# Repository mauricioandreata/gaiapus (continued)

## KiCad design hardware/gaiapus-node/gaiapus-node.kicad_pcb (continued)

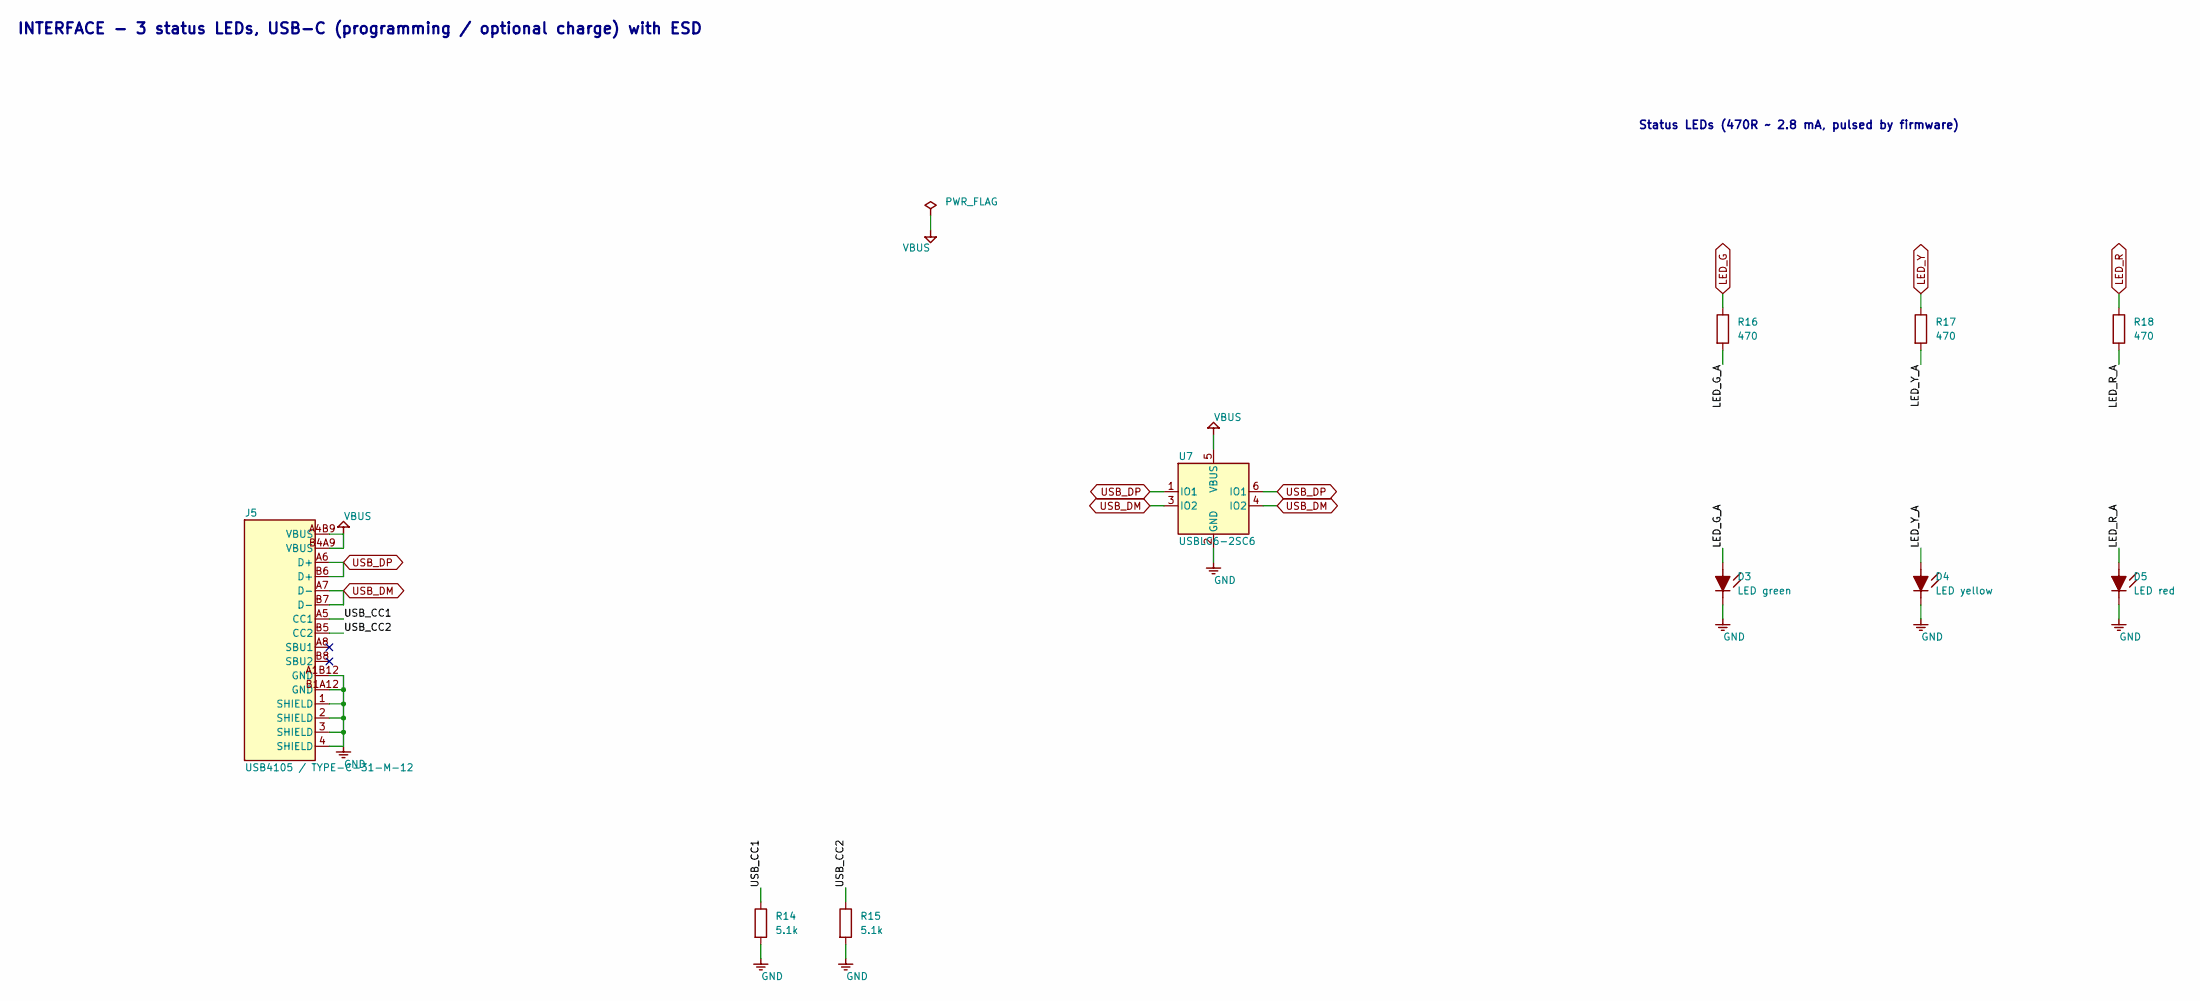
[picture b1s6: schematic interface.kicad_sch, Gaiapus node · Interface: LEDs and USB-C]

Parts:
D3: LED green; LED_0603_1608Metric; LCSC TBD
D4: LED yellow; LED_0603_1608Metric; LCSC TBD
D5: LED red; LED_0603_1608Metric; LCSC TBD
J5: USB4105 / TYPE-C-31-M-12; USB-C_SMD-TYPE-C-31-M-12_1; MPN TYPE-C-31-M-12; LCSC C165948
R14, R15: 5.1k; R_0603_1608Metric; LCSC TBD
R16, R17, R18: 470; R_0603_1608Metric; LCSC TBD
U7: USBLC6-2SC6; SOT-23-6_L2.9-W1.6-P0.95-LS2.8-BL; MPN USBLC6-2SC6; LCSC C7519

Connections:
/Interface/LED_G_A: D3.2 (A), R16.2
/Interface/LED_R_A: D5.2 (A), R18.2
/Interface/LED_Y_A: D4.2 (A), R17.2
/Interface/USB_CC1: J5.A5 (CC1), R14.1
/Interface/USB_CC2: J5.B5 (CC2), R15.1
LED_G: R16.1; also elsewhere on the board
LED_R: R18.1; also elsewhere on the board
LED_Y: R17.1; also elsewhere on the board
USB_DM: J5.A7 (D-), J5.B7 (D-), U7.3 (IO2), U7.4 (IO2); also elsewhere on the board
USB_DP: J5.A6 (D+), J5.B6 (D+), U7.1 (IO1), U7.6 (IO1); also elsewhere on the board
VBUS: J5.A4B9 (VBUS), J5.B4A9 (VBUS), U7.5 (VBUS); also elsewhere on the board

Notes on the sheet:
INTERFACE - 3 status LEDs, USB-C (programming / optional charge) with ESD
Status LEDs (470R ~ 2.8 mA, pulsed by firmware)

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
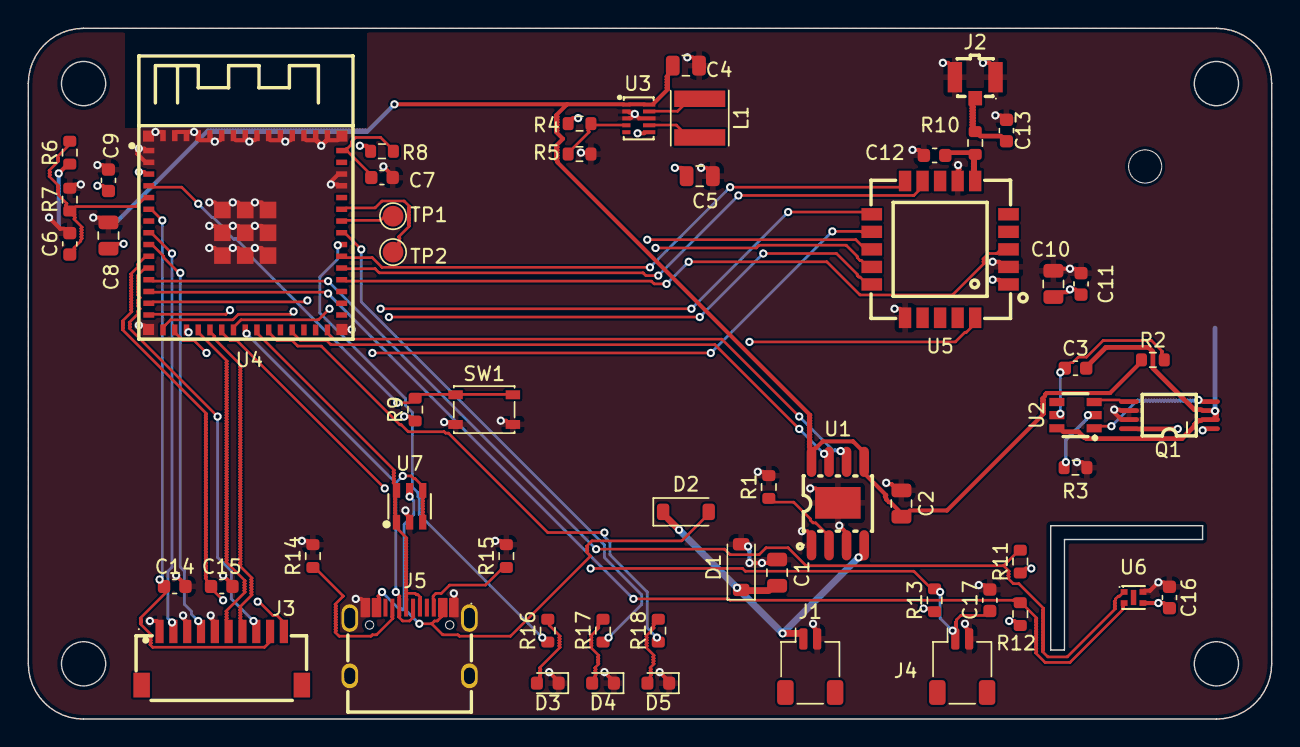
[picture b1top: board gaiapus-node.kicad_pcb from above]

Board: 4 copper layers, 90.0 x 50.0 mm, 58 parts (1 on the bottom side), 53 nets.

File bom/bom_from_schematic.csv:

Board,Refs,Qty,Value,Footprint,Manufacturer,MPN,LCSC,DNP
head,J1,1,SOLAR 5V 60mA,Connector_JST:JST_SH_SM02B-SRSS-TB_1x02-1MP_P1.00mm_Horizontal,JST,SM02B-SRSS-TB,TBD,
head,D1,1,BZT52C6V2,Diode_SMD:D_SOD-123,,BZT52C6V2,TBD,
head,C1 C2 C4 C8 C10,5,10uF,Capacitor_SMD:C_0805_2012Metric,,,TBD,
head,D2,1,B5819W,Diode_SMD:D_SOD-123,,,TBD,
head,U1,1,CN3058E,lcsc:SOIC-8_L4.9-W3.9-P1.27-LS6.0-BL-EP3.3,Consonance,CN3058E,C112011,
head,R1,1,24k 1%,Resistor_SMD:R_0603_1608Metric,,,TBD,
head,BT1,1,18650 LiFePO4,lcsc:BATTERY-SMD_18650-1S-L77.1-W20.7-1,MYOUNG,BH-18650-B1BA002,C2988620,
head,R2,1,100,Resistor_SMD:R_0603_1608Metric,,,TBD,
head,C3 C6 C9 C11 C16,5,100nF,Capacitor_SMD:C_0603_1608Metric,,,TBD,
head,U2,1,HY2112-BB,lcsc:SOT-23-6_L2.9-W1.6-P0.95-LS2.8-BR,HYCON,HY2112-BB,C161942,
head,Q1,1,8205A,lcsc:TSSOP-8_L4.4-W3.0-P0.65-LS6.4-BL,HXY MOSFET,8205A,C5148694,
head,R3,1,2k,Resistor_SMD:R_0603_1608Metric,,,TBD,
head,U3,1,TPS63802,lcsc:VSON-10_L3.0-W2.0-P0.50-TL,Texas Instruments,TPS63802DLAR,C2845237,
head,L1,1,0.47uH,Inductor_SMD:L_Taiyo-Yuden_NR-40xx,,,TBD,
head,C5,1,22uF,Capacitor_SMD:C_0805_2012Metric,,,TBD,
head,R4,1,511k,Resistor_SMD:R_0603_1608Metric,,,TBD,
head,R5,1,91k,Resistor_SMD:R_0603_1608Metric,,,TBD,
head,R6 R7,2,2.2M,Resistor_SMD:R_0603_1608Metric,,,TBD,
head,U4,1,ESP32-S3-MINI-1-N8,lcsc:BULETM-SMD_ESP32-S3-MINI-1-N8,Espressif,ESP32-S3-MINI-1-N8,C2913206,
head,R8 R9 R11 R12,4,10k,Resistor_SMD:R_0603_1608Metric,,,TBD,
head,C7,1,1uF,Capacitor_SMD:C_0603_1608Metric,,,TBD,
head,SW1,1,USER/BOOT,Button_Switch_SMD:SW_SPST_PTS810,,,TBD,
head,TP1,1,TP_TX,TestPoint:TestPoint_Pad_D1.5mm,,,TBD,
head,TP2,1,TP_RX,TestPoint:TestPoint_Pad_D1.5mm,,,TBD,
head,U5,1,E22-900MM22S,lcsc:WIRELM-SMD_20P-L10.0-W10.0-P1.27-TL,EBYTE,E22-900MM22S,C5333985,
head,R10,1,0R,Resistor_SMD:R_0603_1608Metric,,,TBD,
head,C12 C13,2,DNP,Capacitor_SMD:C_0603_1608Metric,,,TBD,DNP
head,J2,1,U.FL-R-SMT-1(80),lcsc:RF-SMD_FRF05002-JSS103M,Hirose,U.FL-R-SMT-1(80),C88374,
head,J3,1,PROBE,lcsc:CONN-SMD_10P-P1.00_SM10B-SRSS-TB-LF-SN,JST,SM10B-SRSS-TB(LF)(SN),C160409,
head,C14 C15 C17,3,10nF,Capacitor_SMD:C_0603_1608Metric,,,TBD,
head,U6,1,SHT40-AD1B-R2,lcsc:DFN-4_L1.5-W1.5-P0.8-TL-EP,Sensirion,SHT40-AD1B-R2,C2909890,
head,J4,1,RAIN,Connector_JST:JST_SH_SM02B-SRSS-TB_1x02-1MP_P1.00mm_Horizontal,JST,SM02B-SRSS-TB,TBD,
head,R13,1,470k,Resistor_SMD:R_0603_1608Metric,,,TBD,
head,J5,1,USB4105 / TYPE-C-31-M-12,lcsc:USB-C_SMD-TYPE-C-31-M-12_1,HRO,TYPE-C-31-M-12,C165948,
head,R14 R15,2,5.1k,Resistor_SMD:R_0603_1608Metric,,,TBD,
head,U7,1,USBLC6-2SC6,lcsc:SOT-23-6_L2.9-W1.6-P0.95-LS2.8-BL,STMicroelectronics,USBLC6-2SC6,C7519,
head,R16 R17 R18,3,470,Resistor_SMD:R_0603_1608Metric,,,TBD,
head,D3,1,LED green,LED_SMD:LED_0603_1608Metric,,,TBD,
head,D4,1,LED yellow,LED_SMD:LED_0603_1608Metric,,,TBD,
head,D5,1,LED red,LED_SMD:LED_0603_1608Metric,,,TBD,
probe,J1,1,HEAD,lcsc:CONN-SMD_10P-P1.00_SM10B-SRSS-TB-LF-SN,JST,SM10B-SRSS-TB(LF)(SN),C160409,
probe,U1 U2,2,74LVC1G14,lcsc:SOT-753_L3.1-W1.7-P0.95-LS3.0-BR,Nexperia,"74LVC1G14GV,125",C131093,
probe,C1 C3,2,100nF,Capacitor_SMD:C_0603_1608Metric,,,TBD,
probe,R1 R3,2,47k,Resistor_SMD:R_0603_1608Metric,,,TBD,
probe,R2 R4,2,100,Resistor_SMD:R_0603_1608Metric,,,TBD,
probe,TP1,1,TP_F15,TestPoint:TestPoint_Pad_D1.5mm,,,TBD,
probe,C2 C4,2,DNP 10pF,Capacitor_SMD:C_0603_1608Metric,,,TBD,DNP
probe,TP2,1,TP_F40,TestPoint:TestPoint_Pad_D1.5mm,,,TBD,
probe,R5 R6,2,10k,Resistor_SMD:R_0603_1608Metric,,,TBD,
probe,RT1,1,NTC 10k 15cm,lcsc:R0603,Murata,NCP18XH103F03RB,C13564,
probe,RT2,1,NTC 10k 40cm,lcsc:R0603,Murata,NCP18XH103F03RB,C13564,

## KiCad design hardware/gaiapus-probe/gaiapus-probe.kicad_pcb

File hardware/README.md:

# Hardware

| Folder | What |
|---|---|
| `gaiapus-node/` | KiCad 8 project of the **head board** (ESP32-S3, LoRa, power, SHT40, rain, LEDs, USB). Root sheet = block diagram. |
| `gaiapus-probe/` | KiCad 8 project of the **probe board** (strip 22 x ~460 mm inside the 32 mm PVC tube): electrodes, oscillators, NTCs. |
| `lib/` | `symbols/gaiapus.kicad_sym` (generated), `footprints/gaiapus.pretty` (electrode), `lcsc.*` (imported from LCSC) |
| `tools/` | generators and checks (below) |

## Tools
| Script | Run when |
|---|---|
| `gen_kicad.py` | after any circuit change: writes both schematics, symbol lib, netlists, `bom/bom_from_schematic.csv` |
| `check_kicad.py` | after `gen_kicad.py`: re-derives connectivity from geometry, must print `RESULT: OK` |
| `gen_footprints.py` | electrode footprint (parametric: width, height, finger, gap) |
| `import_lcsc.cmd` | **on Windows, once**: footprints + 3D models of all LCSC parts (needs Python + internet) |
| `apply_lcsc.py` | after the import: maps footprints, fixes 3D paths, checks pin/pad numbers and pin names against the LCSC symbols |
| `autoplace.py` + `check_placement.py` | first-pass placement into the zones, overlap/edge/hole check |
| `place_head.py` | connectivity-driven floorplan of the head board (positions + rotations), strips routing |
| `fpmove.py` | move/rotate footprints in a board file (90-degree steps) |
| `route.py probe\|head` | grid router (2 layers, 45 deg, vias, GND stitching), clearances from the .kicad_dru; `ROUTE_ONLY`, `ROUTE_FIRST`, `ROUTE_BUDGET`, `ROUTE_RIPUP` (seconds of rip-up and reroute), `ROUTE_MAXHITS` env vars |
| `verify_pcb.py board.kicad_pcb` | independent copper check: connectivity, clearance between nets, copper-to-edge |
| `gen_pcb_outline.py` | board outlines, mounting holes, SHT40 slot and placement boxes (refuses to touch a PCB that already has footprints) |

Close KiCad before regenerating (regeneration overwrites the schematic files).

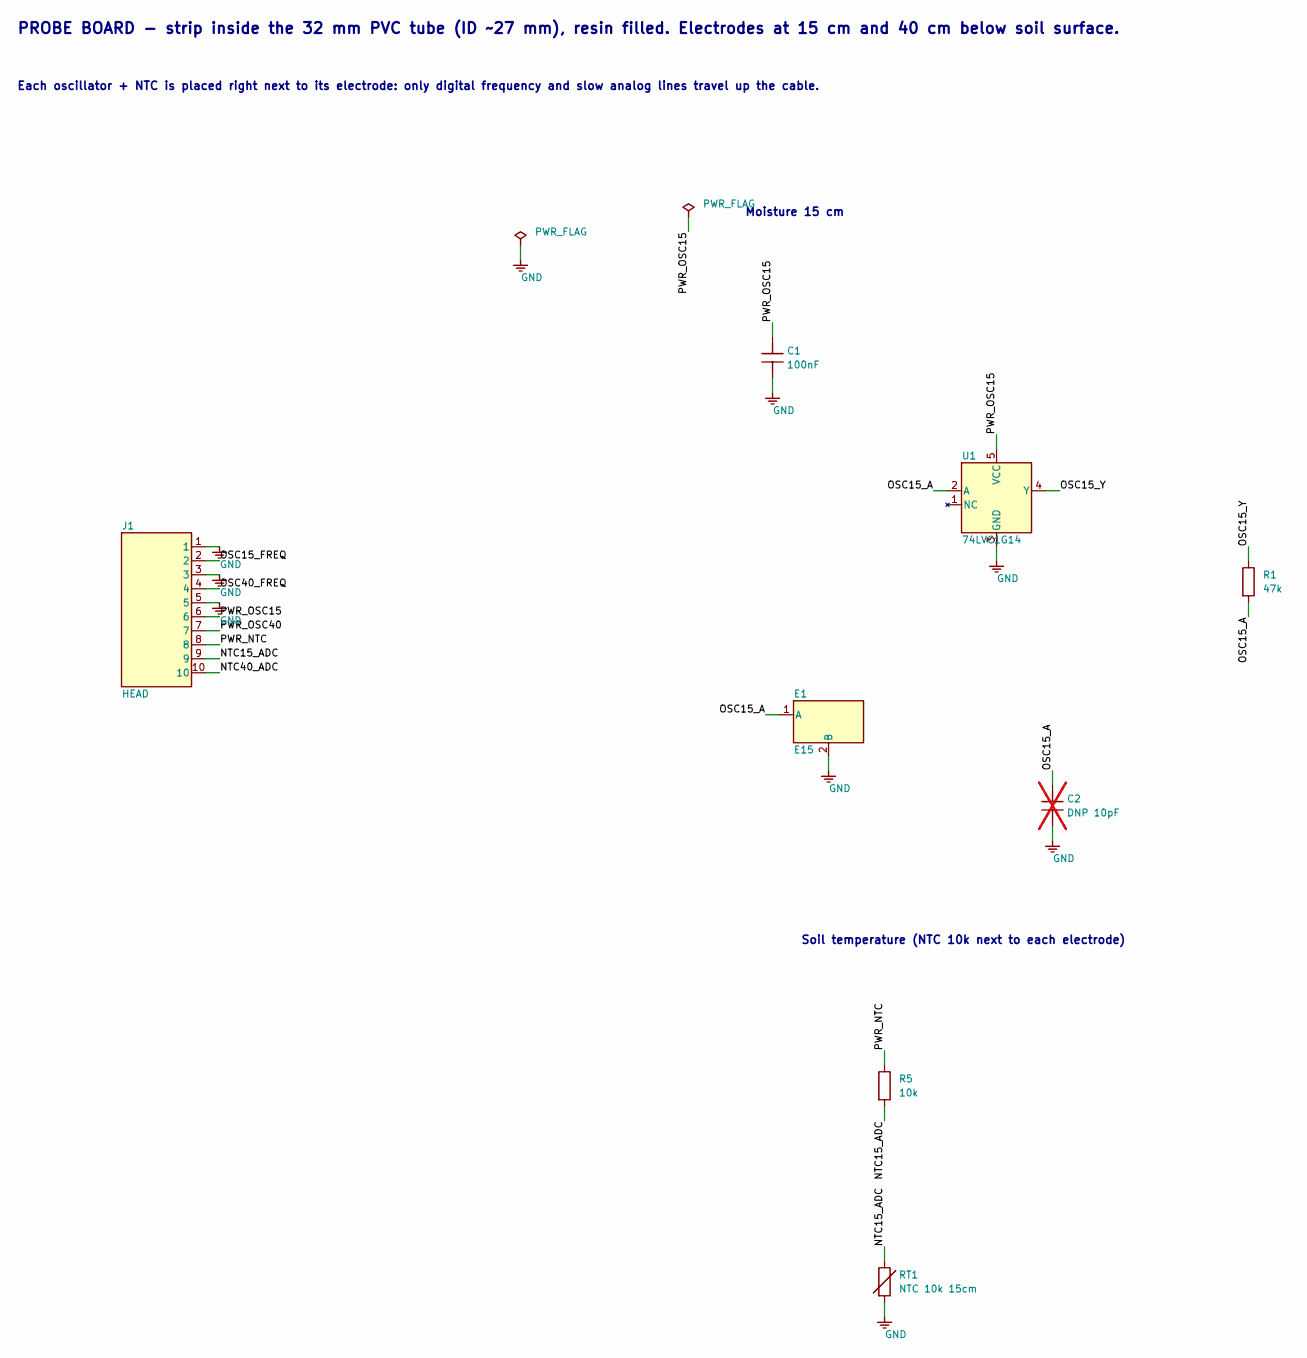
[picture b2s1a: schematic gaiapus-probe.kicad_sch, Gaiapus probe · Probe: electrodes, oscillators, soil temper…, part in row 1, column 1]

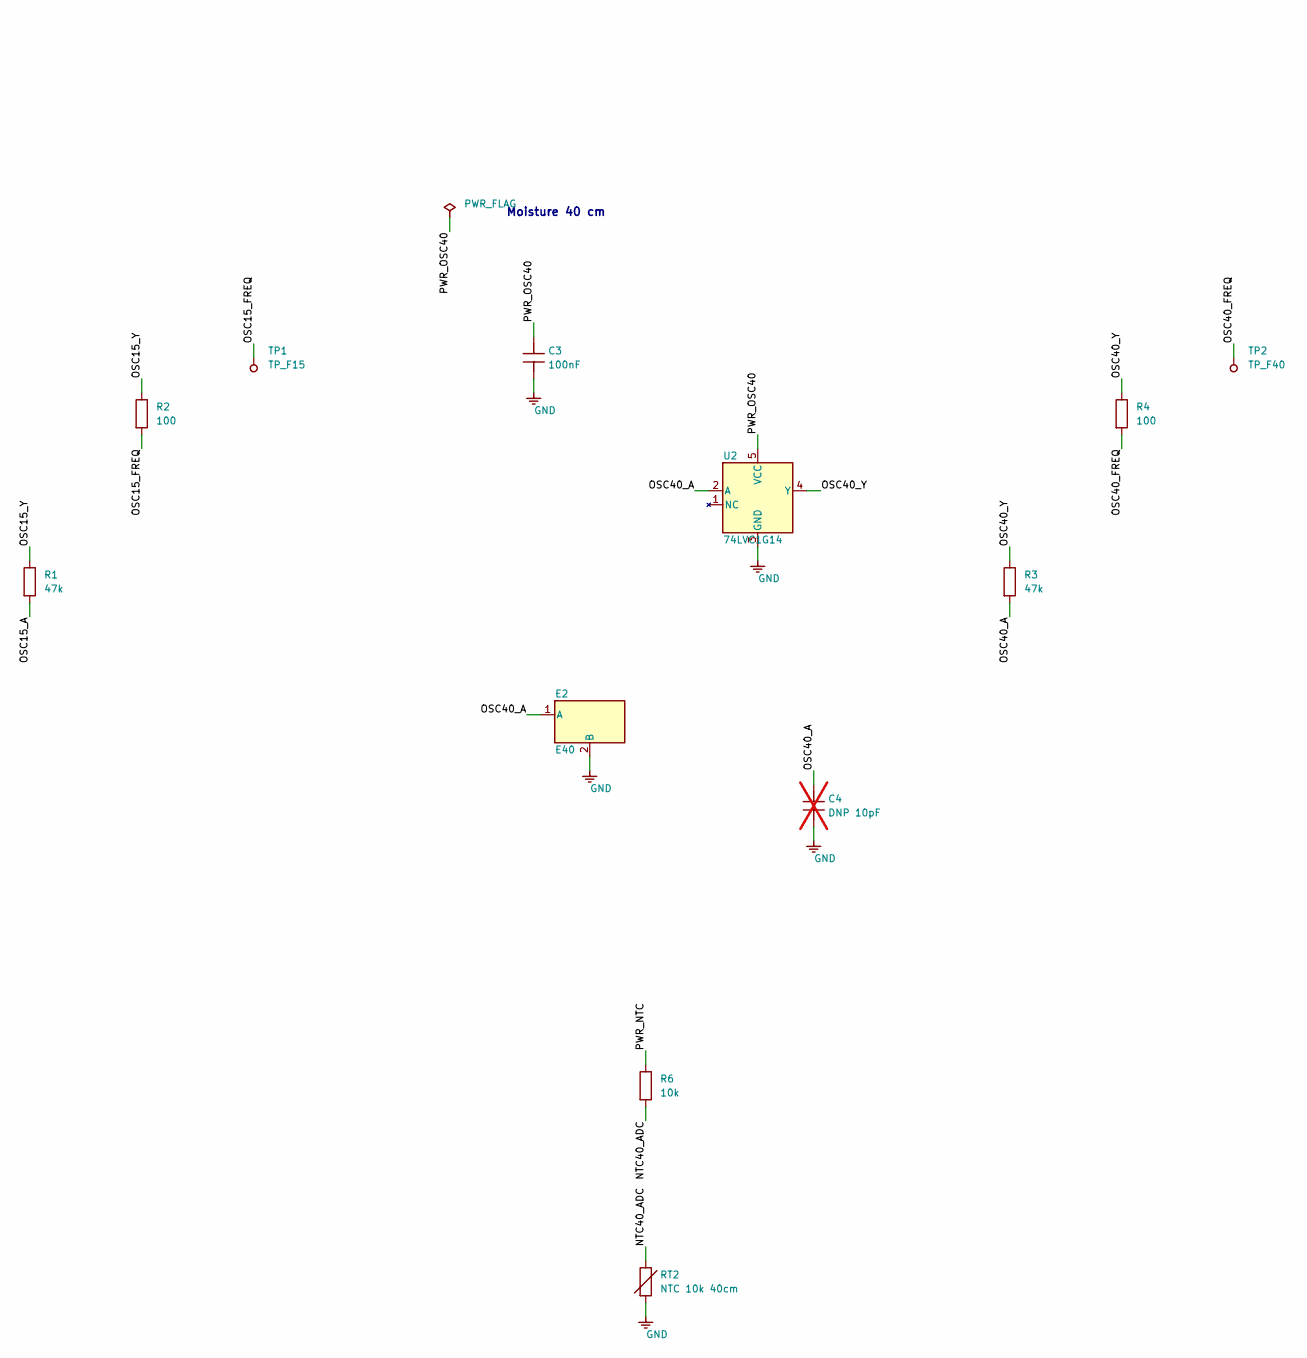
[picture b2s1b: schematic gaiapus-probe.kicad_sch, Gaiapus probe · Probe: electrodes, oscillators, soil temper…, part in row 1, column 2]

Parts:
C1, C3: 100nF; C_0603_1608Metric; LCSC TBD
C2, C4: DNP 10pF; C_0603_1608Metric; LCSC TBD; not fitted
E1: E15; ELECTRODE_IDC_18x40; LCSC TBD
E2: E40; ELECTRODE_IDC_18x40; LCSC TBD
J1: HEAD; CONN-SMD_10P-P1.00_SM10B-SRSS-TB-LF-SN; MPN SM10B-SRSS-TB(LF)(SN); LCSC C160409
R1, R3: 47k; R_0603_1608Metric; LCSC TBD
R2, R4: 100; R_0603_1608Metric; LCSC TBD
R5, R6: 10k; R_0603_1608Metric; LCSC TBD
RT1: NTC 10k 15cm; R0603; MPN NCP18XH103F03RB; LCSC C13564
RT2: NTC 10k 40cm; R0603; MPN NCP18XH103F03RB; LCSC C13564
TP1: TP_F15; TestPoint_Pad_D1.5mm; LCSC TBD
TP2: TP_F40; TestPoint_Pad_D1.5mm; LCSC TBD
U1, U2: 74LVC1G14; SOT-753_L3.1-W1.7-P0.95-LS3.0-BR; MPN 74LVC1G14GV,125; LCSC C131093

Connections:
/NTC15_ADC: J1.9, R5.2, RT1.1
/NTC40_ADC: J1.10, R6.2, RT2.1
/OSC15_A: C2.1, E1.1 (A), R1.2, U1.2 (A)
/OSC15_FREQ: J1.2, R2.2, TP1.1 (TP)
/OSC15_Y: R1.1, R2.1, U1.4 (Y)
/OSC40_A: C4.1, E2.1 (A), R3.2, U2.2 (A)
/OSC40_FREQ: J1.4, R4.2, TP2.1 (TP)
/OSC40_Y: R3.1, R4.1, U2.4 (Y)
/PWR_NTC: J1.8, R5.1, R6.1
/PWR_OSC15: C1.1, J1.6, U1.5 (VCC)
/PWR_OSC40: C3.1, J1.7, U2.5 (VCC)
GND: C1.2, C2.2, C3.2, C4.2, E1.2 (B), E2.2 (B), J1.1, J1.3, J1.5, RT1.2, RT2.2, U1.3 (GND), U2.3 (GND)

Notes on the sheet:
PROBE BOARD - strip inside the 32 mm PVC tube (ID ~27 mm), resin filled. Electrodes at 15 cm and 40 cm below soil surface.
Each oscillator + NTC is placed right next to its electrode: only digital frequency and slow analog lines travel up the cable.
Moisture 15 cm
Moisture 40 cm
Soil temperature (NTC 10k next to each electrode)

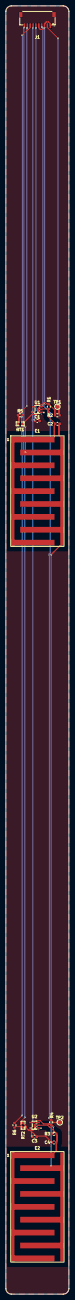
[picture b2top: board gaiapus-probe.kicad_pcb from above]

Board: 2 copper layers, 22.0 x 450.0 mm, 19 parts (0 on the bottom side), 12 nets.

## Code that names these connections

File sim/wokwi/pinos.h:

/* pinos.h - ESP32-S3 pin map. Source of truth: hardware/tools/gen_kicad.py
 * (see docs/hardware-pinmap.md). Bench/Wokwi use the same GPIO numbers.      */
#ifndef GAIAPUS_PINOS_H
#define GAIAPUS_PINOS_H

#define PIN_BTN          0   /* user/boot button, active low                     */
#define PIN_VBAT_ADC     1   /* 2.2M/2.2M divider (x2)                           */
#define PIN_NTC15_ADC    2   /* soil temp 15 cm, NTC to GND, 10k to PWR_NTC       */
#define PIN_OSC15_FREQ   4   /* moisture 15 cm oscillator -> PCNT                */
#define PIN_OSC40_FREQ   5   /* moisture 40 cm oscillator -> PCNT                */
#define PIN_NTC40_ADC    6   /* soil temp 40 cm                                  */
#define PIN_PWR_NTC      7   /* powers both NTC dividers while measuring         */
#define PIN_I2C_SDA      8   /* SHT40 (0x44)                                     */
#define PIN_I2C_SCL      9
#define PIN_LORA_NSS    10
#define PIN_SPI_MOSI    11
#define PIN_SPI_SCK     12
#define PIN_SPI_MISO    13
#define PIN_LORA_DIO1   14   /* RTC GPIO: wakes from deep sleep                  */
#define PIN_PWR_OSC15   15
#define PIN_PWR_OSC40   16
#define PIN_RAIN        17   /* reed to GND, 470k pull-up; RTC GPIO wake         */
#define PIN_LORA_BUSY   18
#define PIN_LED_R       21
#define PIN_LORA_NRST   38
#define PIN_LORA_TXEN   39
#define PIN_LORA_RXEN   40
#define PIN_LED_G       41
#define PIN_LED_Y       42
#define PIN_CHG_ACTIVE  47   /* CN3058E CHRG, open drain, active low             */
#define PIN_CHG_DONE    48   /* CN3058E DONE, open drain, active low             */

#endif
